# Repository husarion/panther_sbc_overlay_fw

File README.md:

# Panther Overlay Firmware
Panther Overlay Firmware is a modified version of [USBCanConverterBasic (UCCB)](https://github.com/UsbCANConverter-UCCbasic) which is open source USB converter for Controller Area Network (CAN). It has been adapted to replace previous Overlays' MCUs (ATTiny). 

**This firmware is dedicated to Panther SBC Overlay versions 1.3+**

## Firmware
The original firmware comes from [ucandevices - USBCanConverterBasic(UCCB)](https://github.com/UsbCANConverter-UCCbasic/UCCBEmbedded) and has been rewritten for STM32F072CB MCU. The main changes made are the MCU change and the implementation of the DMA on the UART interface.

## MCU Flashing
To program the MCU use [CubeProgrammer](https://www.st.com/en/development-tools/stm32cubeprog.html), [ST-Link Utility](https://www.st.com/en/development-tools/stsw-link004.html) and 
select a binary found in **Release** folder or download [Atollic TrueSTUDIO](https://www.st.com/en/development-tools/truestudio.html) and compile the code yourself. Integration with
STM32CubeIDE is yet to be done.
 
## Panther SBC Overlay Integration

### UART improvements

#### UART Reception
UART communication utilizes DMA and STM32 UART Controller's character detection. 
In **slcan** every command is terminated with the **line return** character `\r`. 
With speeds of 4Mbps, UART RX interrupt would occur with every **byte** received, so the DMA
and character match combination is introduced to extend an overall device performance. 

DMA appends every received byte to an ***active buffer***. When `\r` is received, the interrupt is raised, the buffers' content is parsed from text to a raw CAN message.

However, before parsing a message, the ***active buffer*** is swapped, so the reception of the next message
can begin while the previous message is being parsed.

#### UART Transmission
Transmission also utilizes DMA, yet it is not as demanding as the reception. 
After receiving a CAN frame an interrupt raises which switches on a `canRxFlag`.
Then a received frame is parsed to slcan ASCII format, and then it is sent either by an UART
or USB (if connected).

### Panther Lights
Panther Lights are two strips based on APA102 LED modules located on both front and rear bumper. Panther's startup animation is sent by this MCU. 
Another DMA channel is used to transfer an LED color buffer via SPI. This channel is set to
**circular mode**, so the transmission request is called only once at the beginning of the program.
The animation is calculated in the main program loop once every 18ms.

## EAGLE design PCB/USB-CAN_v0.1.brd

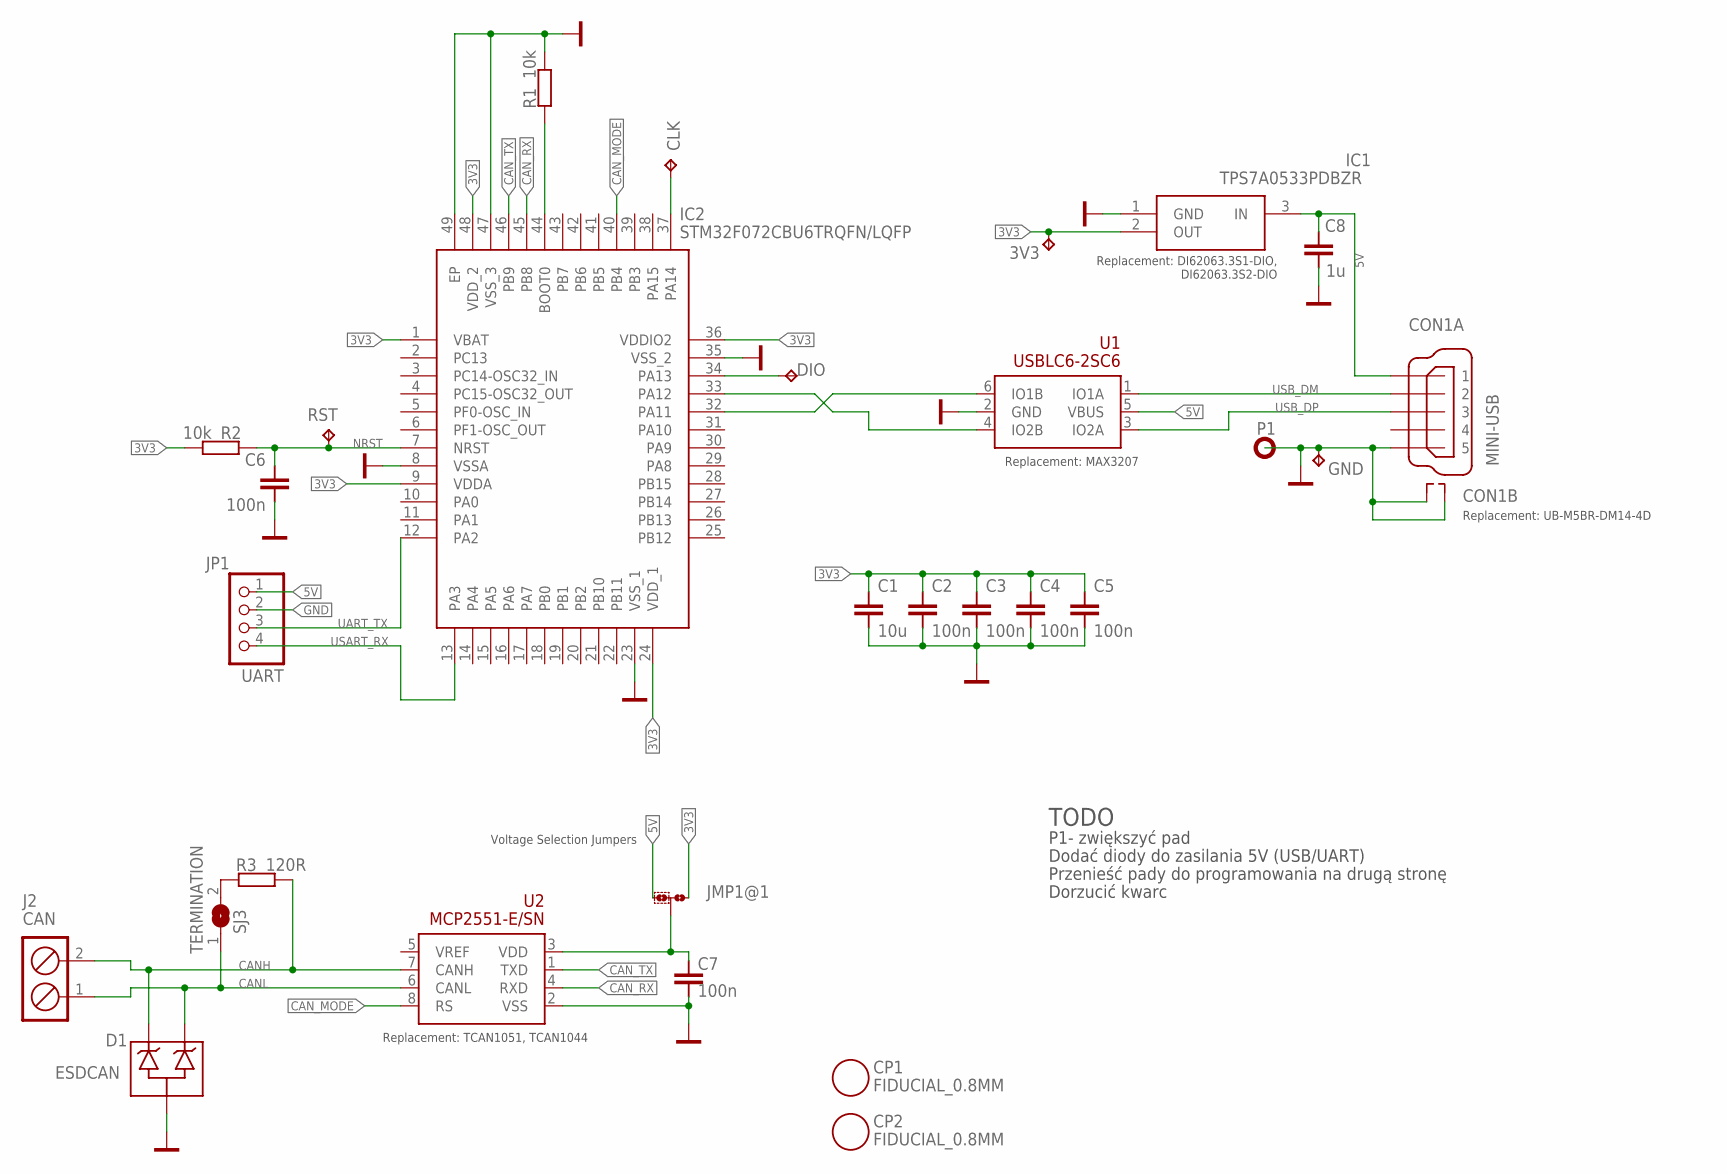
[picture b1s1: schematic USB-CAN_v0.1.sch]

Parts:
3V3: TPTP14R; TP14R
C1: 10u; 0603
C2, C3, C4, C5, C6, C7: 100n; 0603
C8: 1u; 0603
CLK: TPTP14R; TP14R
CON1: MINI-USB; GMSB0522132EU
CP1, CP2: FIDUCIAL_0.8MM; FIDUCIAL_0.8MM_MINI
D1: ESDCAN; SOT323-3L_ST
DIO: TPTP14R; TP14R
GND: TPTP14R; TP14R
IC1: TPS7A0533PDBZR; SOT23
IC2: STM32F072CBU6TRQFN/LQFP; LQFP/QFN48
J2: CAN; SRUB_2PIN_5MM
JMP1: 0R-JUMPC; C0R-JMP
JP1: UART; 1X04
P1: PAD1.3; 1,5/0,9
R1, R2: 10k; 0603
R3: 120R; 0603
RST: TPTP14R; TP14R
SJ3: TERMINATION; SJ
U1: USBLC6-2SC6; SOT23-6L
U2: MCP2551-E/SN; SO8

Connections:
3V3: 3V3.TP, C1.1, C2.1, C3.1, C4.1, C5.1, IC1.2 (OUT), IC2.1 (VBAT), IC2.9 (VDDA), IC2.24 (VDD_1), IC2.36 (VDDIO2), IC2.48 (VDD_2), JMP1.1, R2.2
5V: C8.1, CON1.P1 (1), IC1.3 (IN), JMP1.3, JP1.1, U1.5 (VBUS)
CANH: D1.2, J2.2, R3.2, U2.7 (CANH)
CANL: D1.1, J2.1, SJ3.1, U2.6 (CANL)
CAN_MODE: IC2.40 (PB4), U2.8 (RS)
CAN_RX: IC2.45 (PB8), U2.4 (RXD)
CAN_TX: IC2.46 (PB9), U2.1 (TXD)
GND: C1.2, C2.2, C3.2, C4.2, C5.2, C6.2, C7.2, C8.2, CON1.MH1 (S1), CON1.MH2 (S2), CON1.P5 (5), D1.3, GND.TP, IC1.1 (GND), IC2.8 (VSSA), IC2.23 (VSS_1), IC2.35 (VSS_2), IC2.47 (VSS_3), IC2.49 (EP), JP1.2, P1.1, R1.2, U1.2 (GND), U2.2 (VSS)
unnamed: IC2.44 (BOOT0), R1.1
unnamed: DIO.TP, IC2.34 (PA13)
unnamed: CLK.TP, IC2.37 (PA14)
unnamed: IC2.32 (PA11), U1.6 (IO1B)
unnamed: R3.1, SJ3.2
unnamed: IC2.33 (PA12), U1.4 (IO2B)
NRST: C6.1, IC2.7 (NRST), R2.1, RST.TP
UART_TX: IC2.12 (PA2), JP1.3
USART_RX: IC2.13 (PA3), JP1.4
USB_DM: CON1.P2 (2), U1.1 (IO1A)
USB_DP: CON1.P3 (3), U1.3 (IO2A)
XCR_PWR: C7.1, JMP1.2, U2.3 (VDD)

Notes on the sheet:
Voltage Selection Jumpers
Replacement: TCAN1051, TCAN1044
Replacement: MAX3207
Replacement: DI62063.3S1-DIO, DI62063.3S2-DIO
Replacement: UB-M5BR-DM14-4D
P1- zwiększyć pad
Dodać diody do zasilania 5V (USB/UART)
TODO
Przenieść pady do programowania na drugą stronę
Dorzucić kwarc

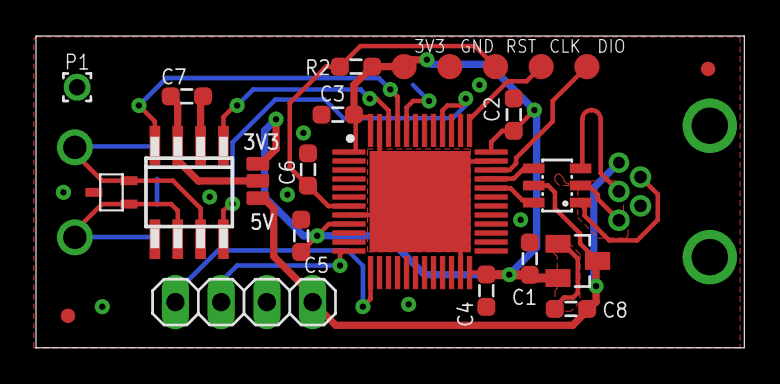
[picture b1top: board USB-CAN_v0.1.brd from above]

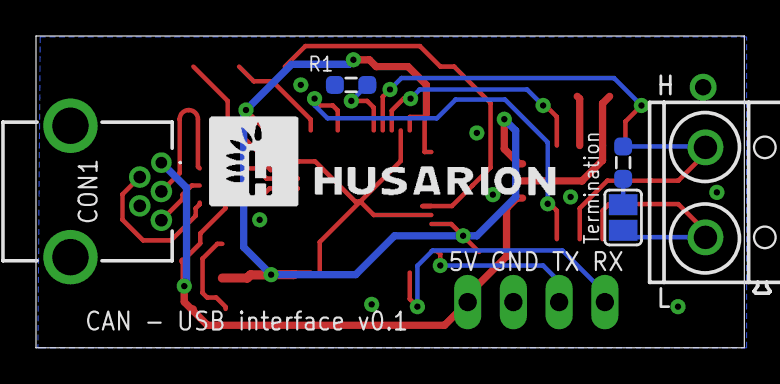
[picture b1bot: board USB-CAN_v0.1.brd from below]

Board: 2 copper layers, 39.3 x 17.3 mm, 30 parts (6 on the bottom side), 20 nets.

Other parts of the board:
U$2: HUS_NAPIS_BOK_5MM

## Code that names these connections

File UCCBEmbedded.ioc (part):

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Mcu.Name=STM32F042C(4-6)Tx
Mcu.Package=LQFP48
Mcu.UserName=STM32F042C6Tx
PA11.Mode=Device
PA11.Signal=USB_DM
PA12.Mode=Device
PA12.Signal=USB_DP
PA2.Mode=Asynchronous
PA2.Signal=USART2_TX
PA3.Mode=Asynchronous
PA3.Signal=USART2_RX
PB8.Mode=Master
PB8.Signal=CAN_RX
PB9.Mode=Master
PB9.Signal=CAN_TX
PF0-OSC_IN.GPIOParameters=GPIO_Label
PF0-OSC_IN.GPIO_Label=CAN_MOD
PF0-OSC_IN.Signal=GPIO_Output
RCC.SYSCLKFreq_VALUE=48000000
RCC.SYSCLKSource=RCC_SYSCLKSOURCE_HSI48
board=UCCBEmbedded

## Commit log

2023-07-19 v1.0
2023-09-15 HusBus initial tests
2023-11-02 UART no loger aborts TX while receiving data
2023-11-07 cleanup
2023-11-08 enabled CTS line, fixed USB
2023-11-21 version 2.0
